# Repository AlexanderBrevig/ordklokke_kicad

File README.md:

# ordklokke_kicad

Check out [ordklokke.no](http://ordklokke.no)

If you want to get this up and running you should clone https://github.com/AlexanderBrevig/KiCADLib in the same location as you clone this repository.

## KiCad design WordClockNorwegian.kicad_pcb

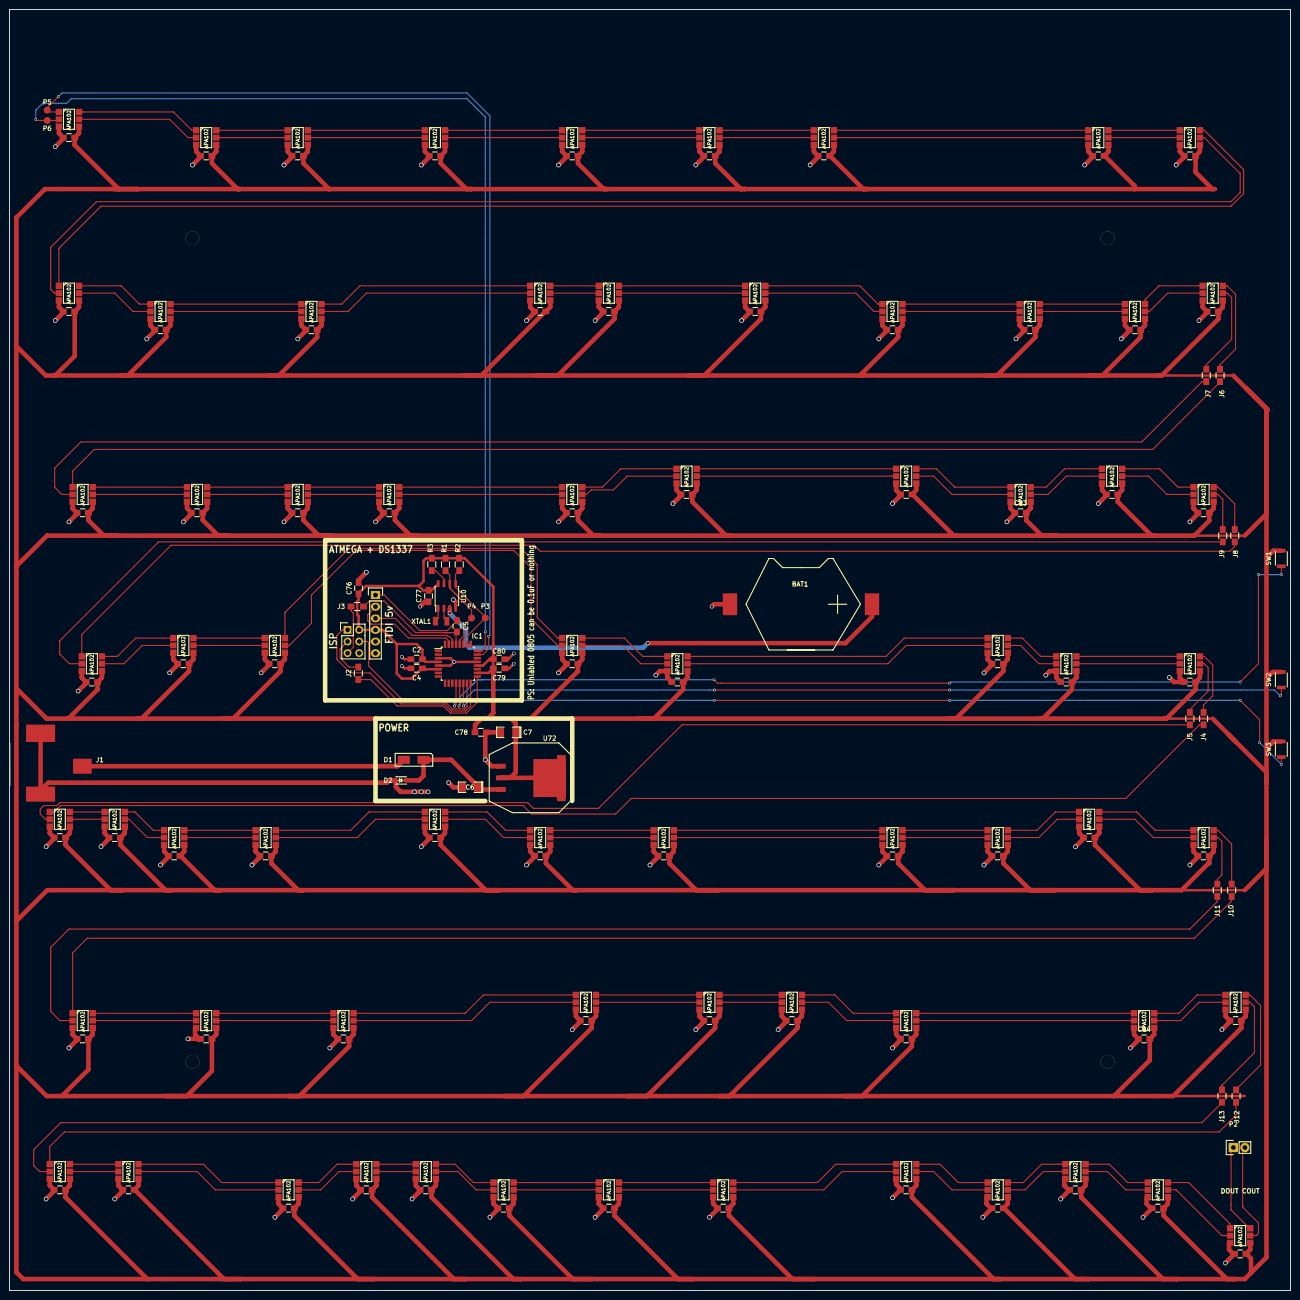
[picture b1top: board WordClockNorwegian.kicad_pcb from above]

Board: 2 copper layers, 280.0 x 280.0 mm, 187 parts (0 on the bottom side), 174 nets.

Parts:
BAT1: BAT_CR2032_MPD-BA2032SM_CPL; BAT_TE_796136-1
C1, C2, C3, C4, C5, C8, C9, C10, C11, C12, C13, C14, C15, C16, C17, C18, C19, C20, C21, C22, C23, C24, C25, C26, C27, C28, C29, C30, C31, C32, C33, C34, C35, C36, C37, C38, C39, C40, C41, C42, C43, C44, C45, C46, C47, C48, C49, C50, C51, C52, C53, C54, C55, C56, C57, C58, C59, C60, C61, C62, C63, C64, C65, C66, C67, C68, C69, C70, C71, C72, C73, C74, C75, C76, C77, C78, C79, C80: 0.1uF; C_0805_HandSoldering
C6, C7: 10uF; SMD-1206_Pol
CON1: AVR-ISP-6; Pin_Header_Straight_2x03
D1: S3JB; DO-214
D2: 12V; SOD-323
H1, H2, H3, H4: M3_mount; M3
IC1: ATMEGA328P-A; TQFP-32_7x7mm_Pitch0.8mm
J1: CONN_Barrel-2.1mm_RASM722X_CPL; RASM722X
J2, J3, J4, J5, J6, J7, J8, J9, J10, J11, J12, J13: 0R; R_0805_HandSoldering
P1: CONN_01X06; Socket_Strip_Straight_1x06
P2: CONN_01X02; Socket_Strip_Straight_1x02
P3, P4, P5, P6: CONN_01X01; Measurement_Point_Round-SMD-Pad_Small
R1, R2: 4.7K; R_0805_HandSoldering
R3: 10K; R_0805_HandSoldering
SW1, SW2, SW3: SW_PUSH; B3U-3000P
U1, U2, U3, U4, U5, U6, U7, U8, U9, U11, U12, U13, U14, U15, U16, U17, U18, U19, U20, U21, U22, U23, U24, U25, U26, U27, U28, U29, U30, U31, U32, U33, U34, U35, U36, U37, U38, U39, U40, U41, U42, U43, U44, U45, U46, U47, U48, U49, U50, U51, U52, U53, U54, U55, U56, U57, U58, U59, U60, U61, U62, U63, U64, U65, U66, U67, U68, U69, U70, U71: APA102
U10: DS1307_CPL; SOIC-8_3.9x4.9mm_Pitch1.27mm
U72: LM1085ISX-5.0; TO-263
XTAL1: XTAL_32.768kHz_CPL; SMD_3.2x1.5mm_XTAL

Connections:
/COUT1: U2.2, U64.5
/COUT2: U3.2, U65.5
/COUT3: U4.2, U66.5
/COUT4: U5.2, U67.5
/COUT5: U6.2, U68.5
/COUT6: J11.2, U7.2
/COUT7: U8.2, U70.5
/COUT8: U9.2, U71.5
/DOUT1: U2.1, U64.6
/DOUT2: U3.1, U65.6
/DOUT3: U4.1, U66.6
/DOUT4: U5.1, U67.6
/DOUT5: U6.1, U68.6
/DOUT6: J10.2, U7.1
/DOUT7: U8.1, U70.6
/DOUT8: U9.1, U71.6
GND: BAT1.2, C1.2, C2.2, C3.2, C4.2, C6.2, C7.2, C8.1, C9.1, C10.1, C11.1, C12.1, C13.1, C14.1, C15.1, C16.1, C17.1, C18.1, C19.1, C20.1, C21.1, C22.1, C23.1, C24.1, C25.1, C26.1, C27.1, C28.1, C29.1, C30.1, C31.1, C32.1, C33.1, C34.1, C35.1, C36.1, C37.1, C38.1, C39.1, C40.1, C41.1, C42.1, C43.1, C44.1, C45.1, C46.1, C47.1, C48.1, C49.1, C50.1, C51.1, C52.1, C53.1, C54.1, C55.1, C56.1, C57.1, C58.1, C59.1, C60.1, C61.1, C62.1, C63.1, C64.1, C65.1, C66.1, C67.1, C68.1, C69.1, C70.1, C71.1, C72.1, C73.1, C74.1, C75.1, C76.1, C77.1, C78.1, C79.1, C80.1, CON1.6, D2.2, IC1.3, IC1.5, IC1.21, J1.1, J1.2, P1.6, U1.3, U2.3, U3.3, U4.3, U5.3, U6.3, U7.3, U8.3, U9.3, U10.4, U11.3, U12.3, U13.3, U14.3, U15.3, U16.3, U17.3, U18.3, U19.3, U20.3, U21.3, U22.3, U23.3, U24.3, U25.3, U26.3, U27.3, U28.3, U29.3, U30.3, U31.3, U32.3, U33.3, U34.3, U35.3, U36.3, U37.3, U38.3, U39.3, U40.3, U41.3, U42.3, U43.3, U44.3, U45.3, U46.3, U47.3, U48.3, U49.3, U50.3, U51.3, U52.3, U53.3, U54.3, U55.3, U56.3, U57.3, U58.3, U59.3, U60.3, U61.3, U62.3, U63.3, U64.3, U65.3, U66.3, U67.3, U68.3, U69.3, U70.3, U71.3, U72.1
MISO: CON1.1, IC1.16
MOSI: CON1.4, IC1.15
unnamed: BAT1.1, U10.3
unnamed: C5.2, P1.1
unnamed: C6.1, D1.1, D2.1, U72.3
unnamed: CON1.3, J2.2
unnamed: CON1.5, J3.2
unnamed: D1.2, J1.3
unnamed: IC1.12, SW1.2
unnamed: IC1.13, SW2.2
unnamed: IC1.14, SW3.2
unnamed: IC1.23, P5.1, U1.1
unnamed: IC1.24, P6.1, U1.2
unnamed: J4.1, U42.6
unnamed: J4.2, U51.1
unnamed: J5.1, U42.5
unnamed: J5.2, U51.2
unnamed: J6.1, U22.6
unnamed: J6.2, U31.1
unnamed: J7.1, U22.5
unnamed: J7.2, U31.2
unnamed: J8.1, U41.6
unnamed: J8.2, U50.1
unnamed: J9.1, U41.5
unnamed: J9.2, U50.2
unnamed: J10.1, U69.6
unnamed: J11.1, U69.5
unnamed: J12.1, U8.6
unnamed: J12.2, U18.1
unnamed: J13.1, U8.5
unnamed: J13.2, U18.2
unnamed: P2.1, U55.6
unnamed: P2.2, U55.5
unnamed: R3.2, U10.7
unnamed: U1.5, U11.2
unnamed: U1.6, U11.1
unnamed: U10.1, XTAL1.1
unnamed: U10.2, XTAL1.2
unnamed: U11.5, U20.2
unnamed: U11.6, U20.1
unnamed: U2.6, U12.1
unnamed: U2.5, U12.2
unnamed: U12.5, U21.2
unnamed: U12.6, U21.1
unnamed: U3.6, U13.1
unnamed: U3.5, U13.2
unnamed: U13.5, U22.2
unnamed: U13.6, U22.1
unnamed: U4.6, U14.1
unnamed: U4.5, U14.2
unnamed: U14.5, U23.2
unnamed: U14.6, U23.1
unnamed: U5.6, U15.1
unnamed: U5.5, U15.2
unnamed: U15.5, U24.2
unnamed: U15.6, U24.1
unnamed: U6.6, U16.1
unnamed: U6.5, U16.2
unnamed: U16.5, U25.2
unnamed: U16.6, U25.1
unnamed: U7.6, U17.1
unnamed: U7.5, U17.2
unnamed: U17.5, U26.2
unnamed: U17.6, U26.1
unnamed: U18.5, U27.2
unnamed: U18.6, U27.1
unnamed: U9.6, U19.1
unnamed: U9.5, U19.2
unnamed: U19.5, U28.2
unnamed: U19.6, U28.1
unnamed: U20.5, U29.2
unnamed: U20.6, U29.1
unnamed: U21.5, U30.2
unnamed: U21.6, U30.1
unnamed: U23.5, U32.2
unnamed: U23.6, U32.1
unnamed: U24.5, U33.2
unnamed: U24.6, U33.1
unnamed: U25.5, U34.2
unnamed: U25.6, U34.1
unnamed: U26.5, U35.2
unnamed: U26.6, U35.1
unnamed: U27.5, U36.2
unnamed: U27.6, U36.1
unnamed: U28.5, U37.2
unnamed: U28.6, U37.1
unnamed: U29.5, U38.2
unnamed: U29.6, U38.1
unnamed: U30.5, U39.2
unnamed: U30.6, U39.1
unnamed: U31.5, U40.2
unnamed: U31.6, U40.1
unnamed: U32.5, U41.2
unnamed: U32.6, U41.1
unnamed: U33.5, U42.2
unnamed: U33.6, U42.1
unnamed: U34.5, U43.2
unnamed: U34.6, U43.1
unnamed: U35.5, U44.2
unnamed: U35.6, U44.1
unnamed: U36.5, U45.2
unnamed: U36.6, U45.1
unnamed: U37.5, U46.2
unnamed: U37.6, U46.1
unnamed: U38.5, U47.2
unnamed: U38.6, U47.1
unnamed: U39.5, U48.2
unnamed: U39.6, U48.1
unnamed: U40.5, U49.2
unnamed: U40.6, U49.1
unnamed: U43.5, U52.2
unnamed: U43.6, U52.1
unnamed: U44.5, U53.2
unnamed: U44.6, U53.1
unnamed: U45.5, U54.2
unnamed: U45.6, U54.1
unnamed: U46.5, U55.2
unnamed: U46.6, U55.1
unnamed: U47.5, U56.2
unnamed: U47.6, U56.1
unnamed: U48.5, U57.2
unnamed: U48.6, U57.1
unnamed: U49.5, U58.2
unnamed: U49.6, U58.1
unnamed: U50.5, U59.2
unnamed: U50.6, U59.1
unnamed: U51.5, U60.2
unnamed: U51.6, U60.1
unnamed: U52.5, U61.2
unnamed: U52.6, U61.1
unnamed: U53.5, U62.2
unnamed: U53.6, U62.1
unnamed: U54.5, U63.2
unnamed: U54.6, U63.1
unnamed: U56.5, U64.2
unnamed: U56.6, U64.1
unnamed: U57.5, U65.2
unnamed: U57.6, U65.1
unnamed: U58.5, U66.2
unnamed: U58.6, U66.1
unnamed: U59.5, U67.2
unnamed: U59.6, U67.1
unnamed: U60.5, U68.2
unnamed: U60.6, U68.1
unnamed: U61.5, U69.2
unnamed: U61.6, U69.1
unnamed: U62.5, U70.2
unnamed: U62.6, U70.1
unnamed: U63.5, U71.2
unnamed: U63.6, U71.1
RST: C5.1, IC1.29, J3.1
RX: IC1.30, P1.3
SCK: IC1.17, J2.1
SCL: IC1.28, P4.1, R1.1, U10.6
SDA: IC1.27, P3.1, R2.1, U10.5
TX: IC1.31, P1.2
VCC: C1.1, C2.1, C3.1, C4.1, C7.1, C8.2, C9.2, C10.2, C11.2, C12.2, C13.2, C14.2, C15.2, C16.2, C17.2, C18.2, C19.2, C20.2, C21.2, C22.2, C23.2, C24.2, C25.2, C26.2, C27.2, C28.2, C29.2, C30.2, C31.2, C32.2, C33.2, C34.2, C35.2, C36.2, C37.2, C38.2, C39.2, C40.2, C41.2, C42.2, C43.2, C44.2, C45.2, C46.2, C47.2, C48.2, C49.2, C50.2, C51.2, C52.2, C53.2, C54.2, C55.2, C56.2, C57.2, C58.2, C59.2, C60.2, C61.2, C62.2, C63.2, C64.2, C65.2, C66.2, C67.2, C68.2, C69.2, C70.2, C71.2, C72.2, C73.2, C74.2, C75.2, C76.2, C77.2, C78.2, C79.2, C80.2, CON1.2, IC1.4, IC1.6, IC1.18, IC1.20, P1.4, R1.2, R2.2, R3.1, SW1.1, SW2.1, SW3.1, U1.4, U2.4, U3.4, U4.4, U5.4, U6.4, U7.4, U8.4, U9.4, U10.8, U11.4, U12.4, U13.4, U14.4, U15.4, U16.4, U17.4, U18.4, U19.4, U20.4, U21.4, U22.4, U23.4, U24.4, U25.4, U26.4, U27.4, U28.4, U29.4, U30.4, U31.4, U32.4, U33.4, U34.4, U35.4, U36.4, U37.4, U38.4, U39.4, U40.4, U41.4, U42.4, U43.4, U44.4, U45.4, U46.4, U47.4, U48.4, U49.4, U50.4, U51.4, U52.4, U53.4, U54.4, U55.4, U56.4, U57.4, U58.4, U59.4, U60.4, U61.4, U62.4, U63.4, U64.4, U65.4, U66.4, U67.4, U68.4, U69.4, U70.4, U71.4, U72.2

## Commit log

2015-09-03 initial commit, rev 0.6
2015-09-03 add silk
2015-09-04 HUGE update plus add ignore for bak files
2015-09-04 initial readme
2015-09-04 before sendoff, one more check to go
2015-09-05 tweaks
